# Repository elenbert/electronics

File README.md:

Repository for my electronics projects:

* allsky camera
* ztsh autoguide system
* power supply

CAD: Eagle Version 7.2.0 for Linux

Additional: schematic png's

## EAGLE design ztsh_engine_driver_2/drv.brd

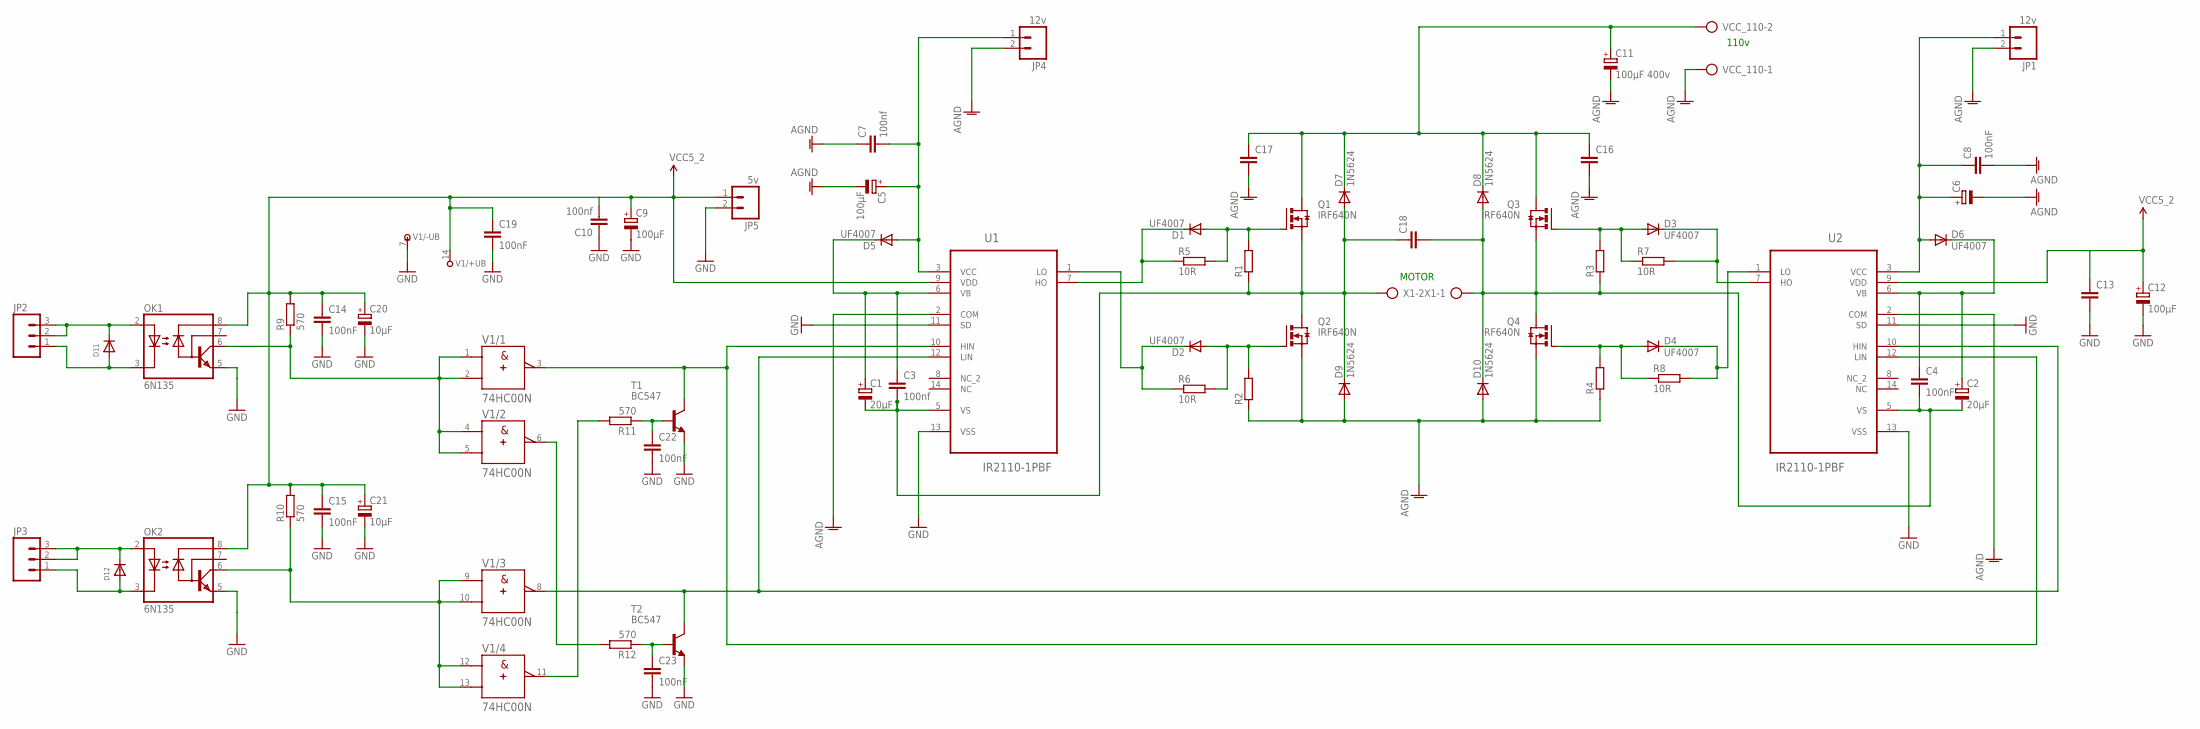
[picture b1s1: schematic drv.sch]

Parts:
C1, C2: 20µF; E2,5-6E
C3, C10: 100nf; C0805
C4: 100nF; C0504
C5, C9, C12: 100µF; E2-5
C6: CPOL-EUE2-5; E2-5
C7: 100nf; C1310
C8, C14, C15, C19, C22, C23: 100nF; C0805
C11: 100µF 400v; EB25D
C13: C-EUC0805; C0805
C16, C17: C5/3; C5B3
C18: C-EU150-091X182; C150-091X182
C20, C21: 10µF; E2-5
D1, D2, D3, D4, D5, D6: UF4007; DIODE-1N4001-KIT
D7, D8, D9, D10: 1N5624; DO201-15
D11, D12: DIODEDO-1N4148; DO-1N4148
JP1, JP4: 12v; JST-2-PTH-VERT
JP2, JP3: M03LOCK; 1X03_LOCK
JP5: 5v; JST-2-PTH-VERT
OK1, OK2: 6N135; DIL08
Q1, Q2, Q3, Q4: IRF640N; TO262-V
R1, R2, R3, R4: R-EU_0207/12; 0207/12
R5, R6, R7, R8: 10R; 0207/12
R9, R10, R11, R12: 570; R0805
T1, T2: BC547; TO92
U1, U2: IR2110-1PBF; DIP254P762X533-14
V1: 74HC00N; DIL14
VCC_110: AK300/2
X1: AK300/2

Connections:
AGND: C5.-, C6.-, C7.1, C8.2, C11.-, C16.2, C17.2, D9.A, D10.A, JP1.2, JP4.2, Q2.3 (S), Q4.3 (S), R2.1, R4.1, U1.2 (COM), U2.2 (COM), VCC_110.1
GND: C9.-, C10.1, C12.-, C13.2, C14.2, C15.2, C19.2, C20.-, C21.-, C22.2, C23.2, JP5.2, T1.1 (E), T2.1 (E), U1.11 (SD), U1.13 (VSS), U2.11 (SD), U2.13 (VSS), V1.7 (-UB)
unnamed: D1.A, Q1.1 (G), R1.2, R5.2
unnamed: D11.C, JP2.2, JP2.3, OK1.2 (A)
unnamed: D2.A, Q2.1 (G), R2.2, R6.2
unnamed: D1.C, R5.1, U1.7 (HO)
unnamed: D11.A, JP2.1, OK1.3 (C)
unnamed: D2.C, R6.1, U1.1 (LO)
unnamed: OK2.6 (VO), R10.1, V1.9 (A), V1.10 (B), V1.12 (A), V1.13 (B)
unnamed: D3.A, Q3.1 (G), R3.2, R7.1
unnamed: D3.C, R7.2, U2.7 (HO)
unnamed: D4.C, R8.2, U2.1 (LO)
unnamed: D12.A, JP3.1, OK2.3 (C)
unnamed: OK1.6 (VO), R9.1, V1.1 (A), V1.2 (B), V1.4 (A), V1.5 (B)
unnamed: D4.A, Q4.1 (G), R4.2, R8.1
unnamed: C1.+, C3.1, D5.C, U1.6 (VB)
unnamed: T1.3 (C), U1.10 (HIN), U2.12 (LIN), V1.3 (Y)
unnamed: C2.+, C4.1, D6.C, U2.6 (VB)
unnamed: T2.3 (C), U1.12 (LIN), U2.10 (HIN), V1.8 (Y)
unnamed: R11.2, V1.11 (Y)
unnamed: C22.1, R11.1, T1.2 (B)
unnamed: C23.1, R12.1, T2.2 (B)
unnamed: R12.2, V1.6 (Y)
unnamed: D12.C, JP3.2, JP3.3, OK2.2 (A)
OUT1: C2.-, C4.2, C18.2, D8.A, D10.C, Q3.3 (S), Q4.2 (D), R3.1, U2.5 (VS), X1.1
OUT2: C1.-, C3.2, C18.1, D7.A, D9.C, Q1.3 (S), Q2.2 (D), R1.1, U1.5 (VS), X1.2
VCC: C9.+, C10.2, C12.+, C13.1, C14.1, C15.1, C19.1, C20.+, C21.+, JP5.1, OK1.8 (VCC), OK2.8 (VCC), R9.2, R10.2, U1.9 (VDD), U2.9 (VDD), V1.14 (+UB)
VCC_12_1: C5.+, C7.2, D5.A, JP4.1, U1.3 (VCC)
VCC_12_2: C6.+, C8.1, D6.A, JP1.1, U2.3 (VCC)
VCC_110: C11.+, C16.1, C17.1, D7.C, D8.C, Q1.2 (D), Q3.2 (D), VCC_110.2

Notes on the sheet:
110v
MOTOR

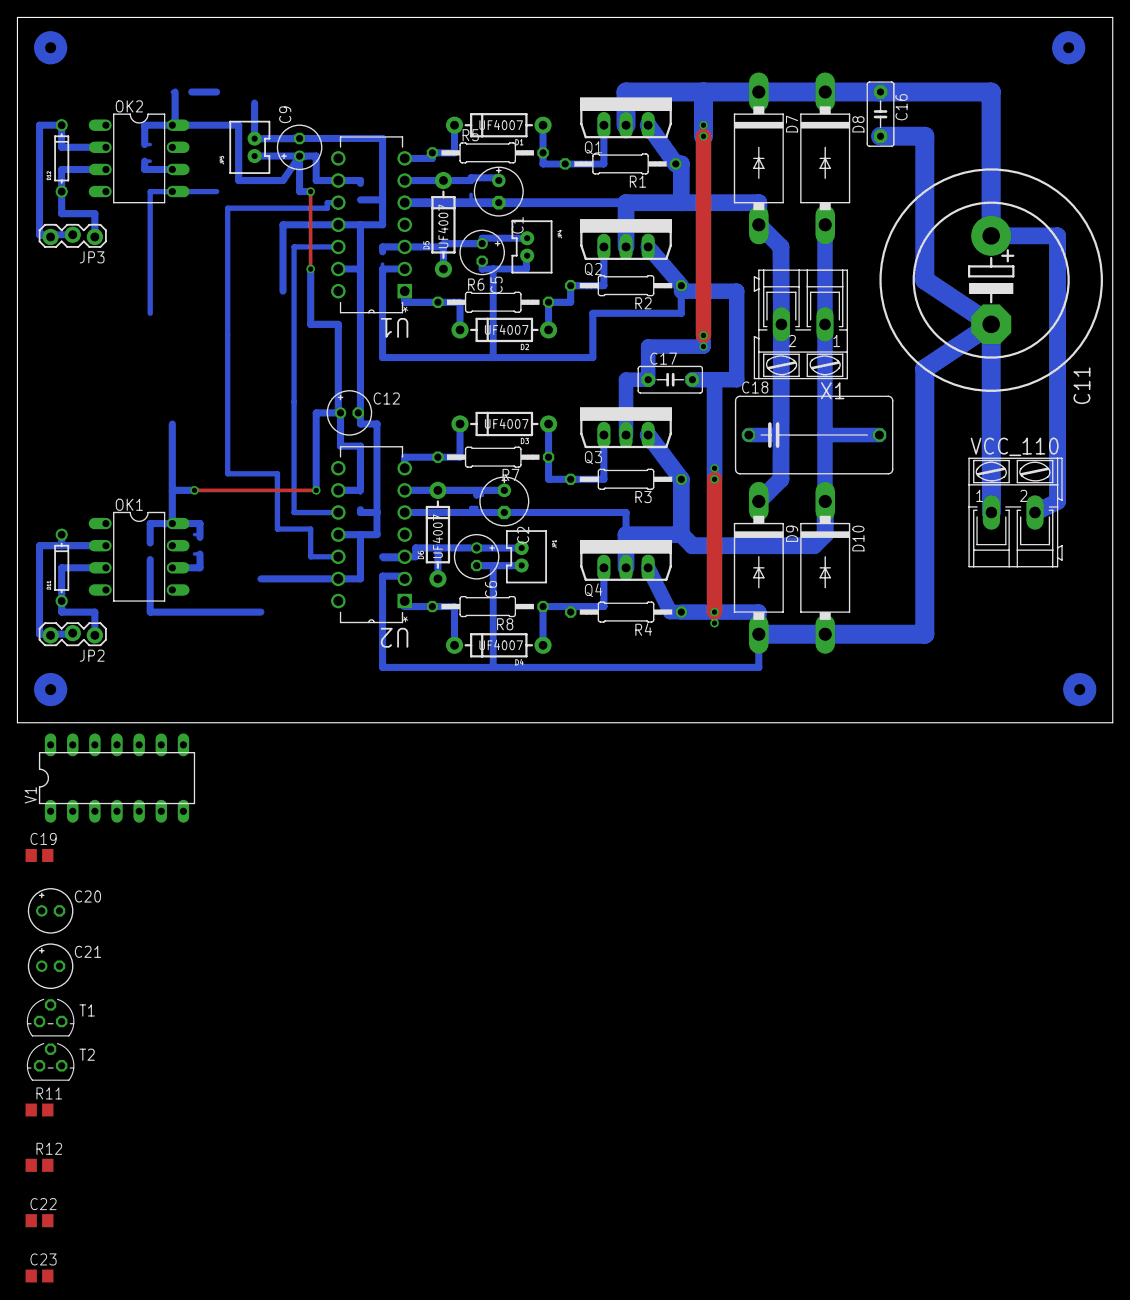
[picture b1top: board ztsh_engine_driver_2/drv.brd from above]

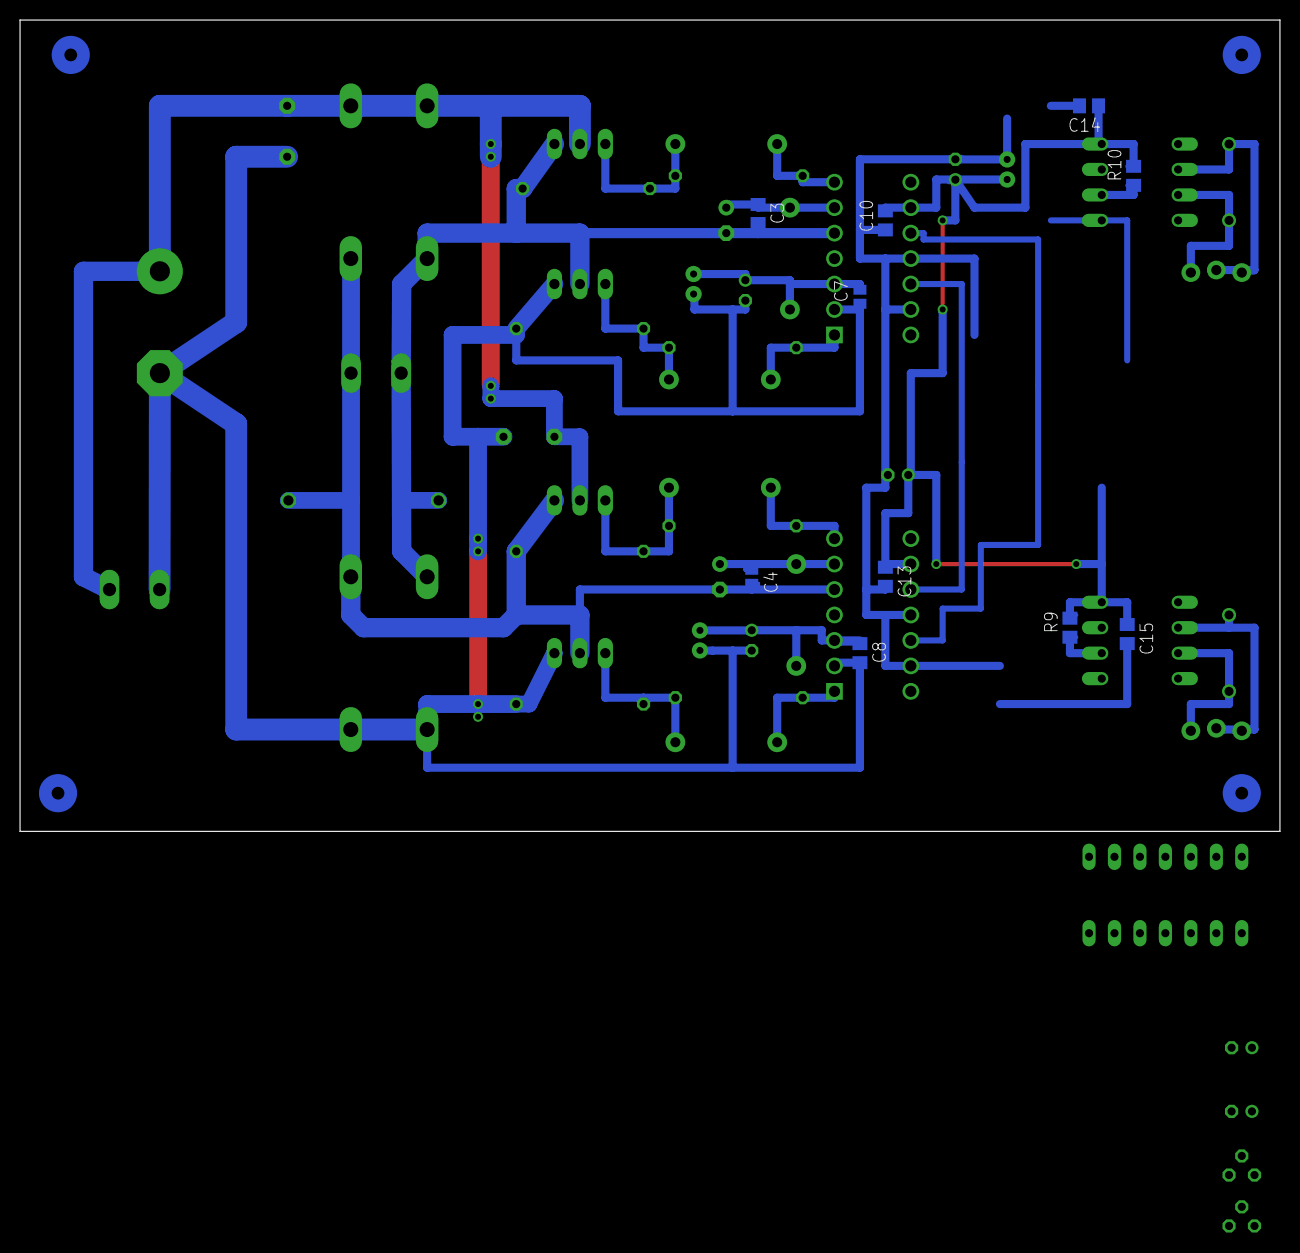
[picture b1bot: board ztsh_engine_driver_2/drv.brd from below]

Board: 2 copper layers, 125.7 x 80.9 mm, 65 parts (10 on the bottom side), 30 nets.

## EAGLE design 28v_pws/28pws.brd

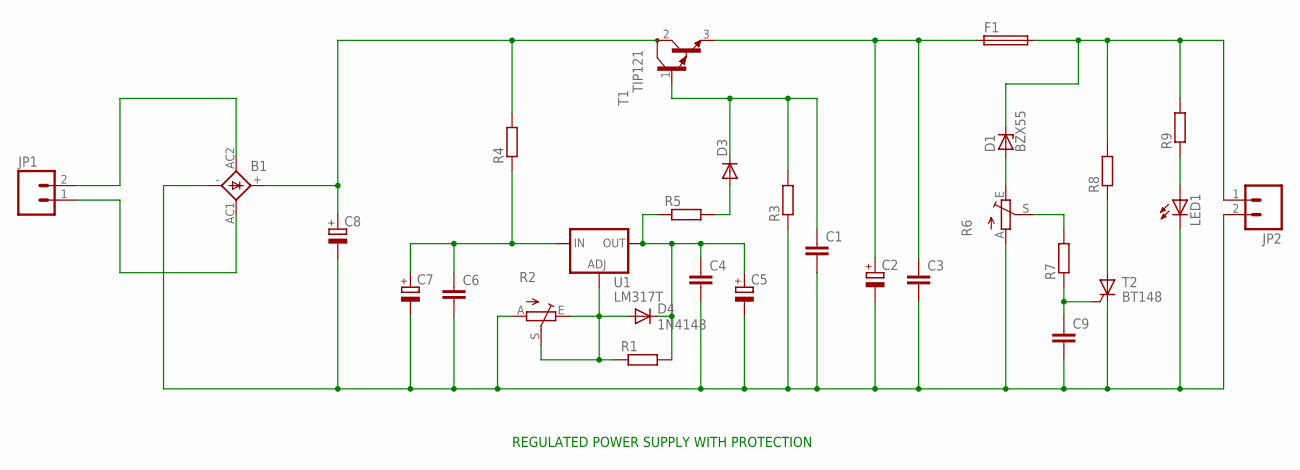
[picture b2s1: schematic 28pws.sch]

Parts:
B1: GBU4S
C1, C3, C4, C6, C9: C-EU025-025X050; C025-025X050
C2: CPOL-EUE5-13; E5-13
C5, C7: CPOL-EUE2.5-5; E2,5-5
C8: CPOL-EUE7.5-16; E7,5-16
D1: BZX55; DO35Z10
D3: DIODE-DO41-7.6; DO41-7.6
D4: 1N4148; DO35-7
F1: 19560
JP1, JP2: M02POGO_PIN_HOLES_ONLY; 1X02_PP_HOLES_ONLY
LED1: LED5MM
R1, R9: R-EU_0204/7; 0204/7
R2: TRIM_EU-RJ9W; RJ9W
R3, R5: R-EU_0204/2V; 0204V
R4: R-EU_0411/3V; 0411V
R6: TRIM_EU-B25P; B25P
R7: R-EU_0207/10; 0207/10
R8: R-EU_VTA54; VTA54
T1: TIP121; TO220
T2: BT148; SOT82S
U1: LM317T; TO220-ADJ

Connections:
GND: B1.-, C1.2, C2.-, C3.2, C4.2, C5.-, C6.2, C7.-, C8.-, C9.2, JP2.2, LED1.K (C), R2.A, R3.1, R6.A, T2.C
unnamed: C1.1, D3.C, R3.2, T1.1 (B)
unnamed: D1.C, F1.2, JP2.1, R8.2, R9.2
unnamed: R6.S, R7.2
unnamed: C2.+, C3.1, F1.1, T1.3 (E)
unnamed: C4.1, C5.+, D4.C, R1.2, R5.1, U1.OUT
unnamed: C6.1, C7.+, R4.1, U1.IN
unnamed: D4.A, R1.1, R2.E, R2.S, U1.ADJ
unnamed: B1.AC2 (AC1), JP1.2
unnamed: D3.A, R5.2
unnamed: B1.+, C8.+, R4.2, T1.2 (C)
unnamed: B1.AC1 (AC2), JP1.1
unnamed: C9.1, R7.1, T2.G
unnamed: D1.A, R6.E
unnamed: LED1.A, R9.1
unnamed: R8.1, T2.A

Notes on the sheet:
REGULATED POWER SUPPLY WITH PROTECTION

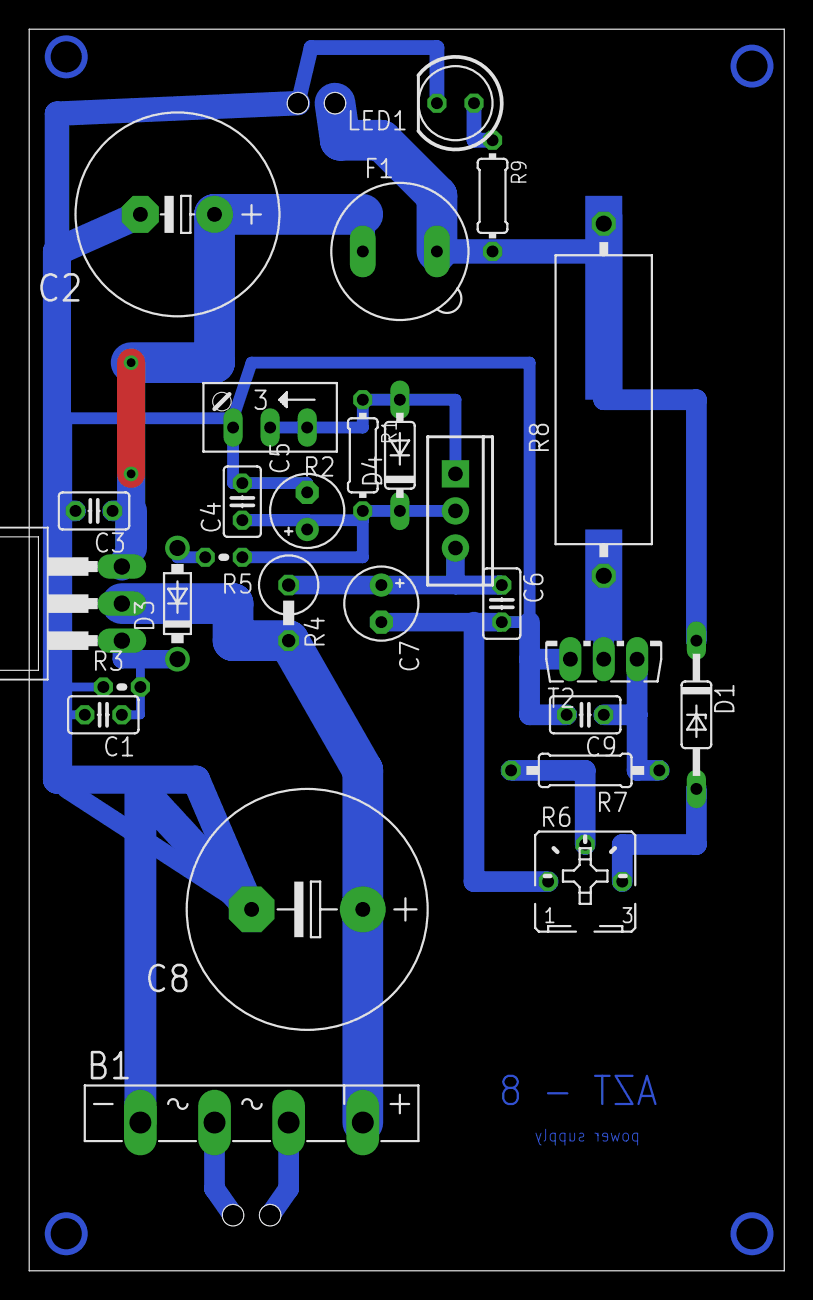
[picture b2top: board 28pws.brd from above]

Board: 2 copper layers, 51.7 x 85.1 mm, 29 parts (0 on the bottom side), 16 nets.

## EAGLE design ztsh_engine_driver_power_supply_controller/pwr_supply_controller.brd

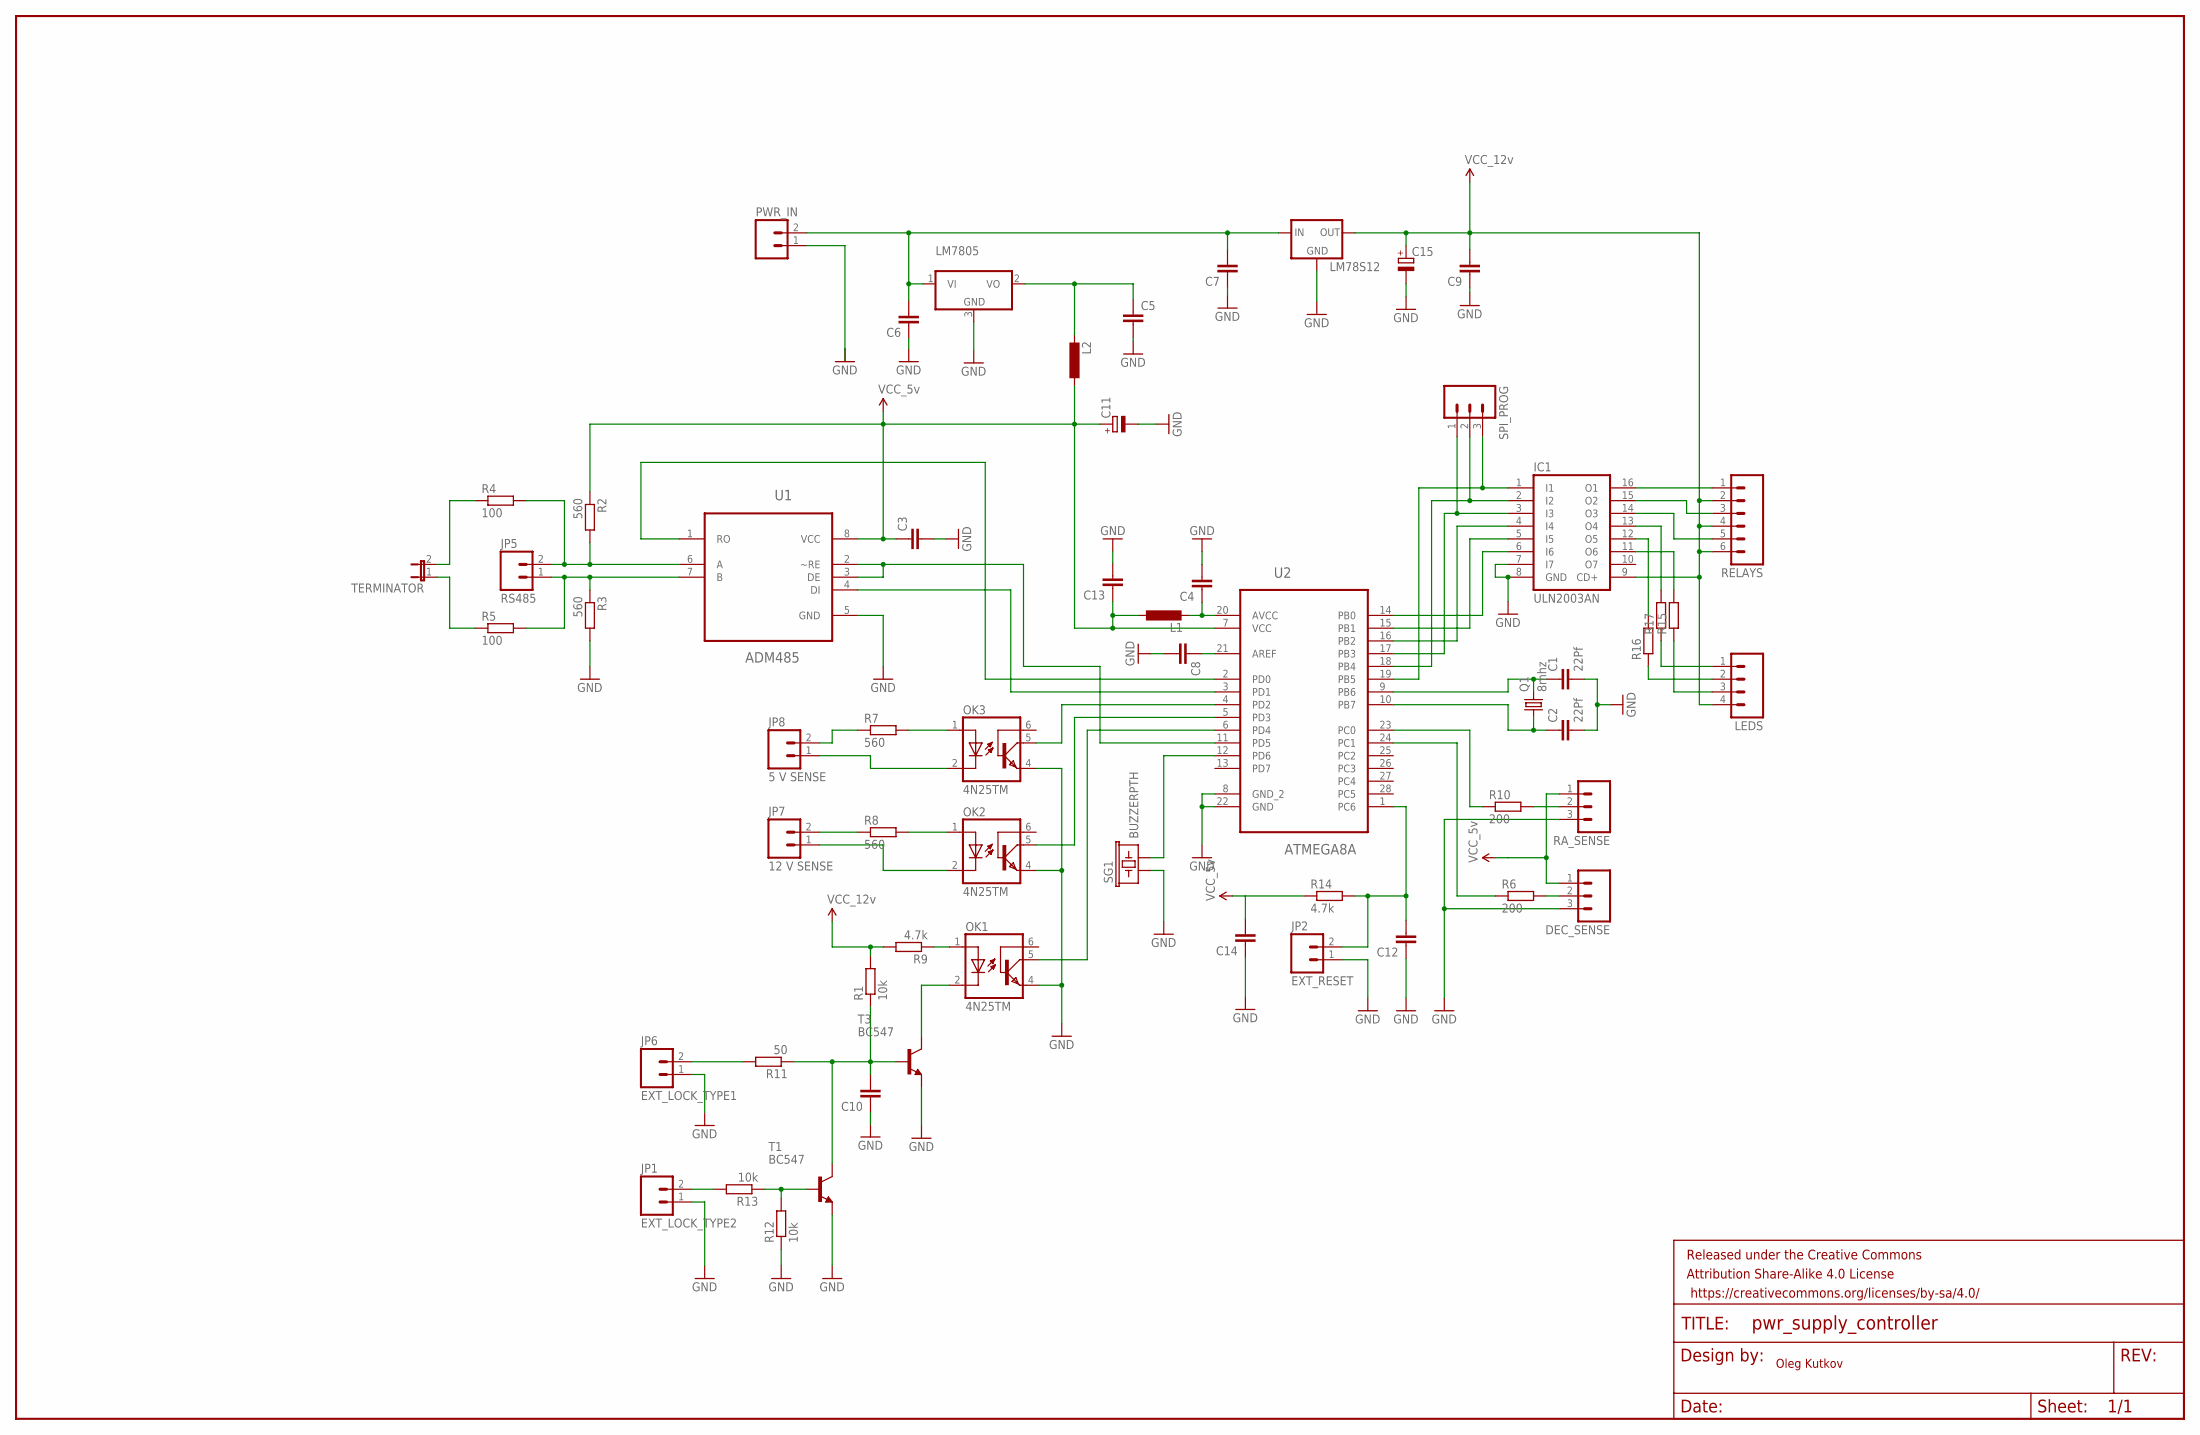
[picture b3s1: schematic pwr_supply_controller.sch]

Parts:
C1, C2: 22Pf; C0603K
C3, C4, C5, C8, C10, C12, C13, C14: C-EUC0603K; C0603K
C6, C7, C9: C-EUC0805; C0805
C11: CPOL-EUE2-5; E2-5
C15: CPOL-EUE3.5-8; E3,5-8
DEC_SENSE: M03PTH; 1X03
FRAME1: FRAME-LEDGER; CREATIVE_COMMONS
IC1: ULN2003AN; DIL16
JP1: EXT_LOCK_TYPE2; JST-2-PTH-VERT
JP2: EXT_RESET; 1X02
JP5: RS485; JST-2-PTH-VERT
JP6: EXT_LOCK_TYPE1; JST-2-PTH-VERT
JP7: 12 V SENSE; JST-2-PTH-VERT
JP8: 5 V SENSE; JST-2-PTH-VERT
L1, L2: L-EU0204/7; 0204/7
LEDS: M04PTH; 1X04
LM78S12: V_REG_78XX-TO-220; TO-220-ALT
LM7805: 7808DT; TO252
OK1, OK2, OK3: 4N25TM; DIL6-04
PWR_IN: M02JST-PTH-VERT; JST-2-PTH-VERT
Q1: 8mhz; HC49/S
R1, R12, R13: 10k; 0204/7
R2, R3: 560; M0805
R4: 100; R0805
R5: 100; M0805
R6, R10: 200; M0805
R7, R8: 560; 0204/7
R9: 4.7k; 0204/7
R11: 50; 0204/7
R14: 4.7k; M0805
R15, R16, R17: R-EU_M0805; M0805
RA_SENSE: M03PTH; 1X03
RELAYS: M06POLAR; MOLEX-1X6
SG1: BUZZERPTH; BUZZER-12MM
SPI_PROG: M03PTH; 1X03
T1, T3: BC547; TO92
TERMINATOR: JUMPER-2PTH_LOCK; 1X02_LOCK
U1: ADM485; SOIC127P600X175-8N
U2: ATMEGA8A; DIP254P762X457-28

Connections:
GND: C1.2, C2.2, C3.2, C4.2, C5.2, C6.1, C7.1, C8.2, C9.1, C10.1, C11.-, C12.1, C13.2, C14.1, C15.-, DEC_SENSE.3, IC1.7 (I7), IC1.8 (GND), JP1.1, JP2.1, JP6.1, LM78S12.GND, LM7805.3 (GND), OK1.4 (EMI), OK2.4 (EMI), OK3.4 (EMI), PWR_IN.1, R3.2, R12.1, RA_SENSE.3, SG1.+ (1), T1.1 (E), T3.1 (E), U1.5 (GND), U2.8 (GND_2), U2.22 (GND)
unnamed: C1.1, Q1.2, U2.9 (PB6)
unnamed: C2.1, Q1.1, U2.10 (PB7)
unnamed: OK3.5 (COL), U2.4 (PD2)
unnamed: OK2.5 (COL), U2.5 (PD3)
unnamed: OK3.1 (A), R7.2
unnamed: OK1.5 (COL), U2.6 (PD4)
unnamed: C4.1, L1.2, U2.20 (AVCC)
unnamed: R10.2, RA_SENSE.2
unnamed: U1.1 (RO), U2.2 (PD0)
unnamed: C8.1, U2.21 (AREF)
unnamed: U1.4 (DI), U2.3 (PD1)
unnamed: U1.2 (~RE), U1.3 (DE), U2.11 (PD5)
unnamed: JP5.2, R2.2, R4.2, U1.6 (A)
unnamed: JP5.1, R3.1, R5.2, U1.7 (B)
unnamed: R4.1, TERMINATOR.2
unnamed: R5.1, TERMINATOR.1
unnamed: C6.2, C7.2, LM78S12.IN, LM7805.1 (VI), PWR_IN.2
unnamed: DEC_SENSE.2, R6.2
unnamed: IC1.6 (I6), U2.14 (PB0)
unnamed: IC1.5 (I5), U2.15 (PB1)
unnamed: IC1.4 (I4), U2.16 (PB2)
unnamed: IC1.3 (I3), SPI_PROG.1, U2.17 (PB3)
unnamed: IC1.2 (I2), SPI_PROG.2, U2.18 (PB4)
unnamed: IC1.1 (I1), SPI_PROG.3, U2.19 (PB5)
unnamed: R10.1, U2.23 (PC0)
unnamed: R6.1, U2.24 (PC1)
unnamed: IC1.16 (O1), RELAYS.1
unnamed: IC1.15 (O2), RELAYS.3
unnamed: IC1.14 (O3), RELAYS.5
unnamed: JP6.2, R11.2
unnamed: LEDS.1, R17.1
unnamed: LEDS.2, R16.1
unnamed: IC1.11 (O6), R15.2
unnamed: SG1.- (2), U2.12 (PD6)
unnamed: JP8.2, R7.1
unnamed: JP8.1, OK3.2 (C)
unnamed: OK2.1 (A), R8.2
unnamed: JP7.2, R8.1
unnamed: JP7.1, OK2.2 (C)
unnamed: C10.2, R1.1, R11.1, T1.3 (C), T3.2 (B)
unnamed: R12.2, R13.1, T1.2 (B)
unnamed: OK1.1 (A), R9.1
unnamed: C5.1, L2.2, LM7805.2 (VO)
unnamed: OK1.2 (C), T3.3 (C)
unnamed: JP1.2, R13.2
unnamed: C12.2, JP2.2, R14.2, U2.1 (PC6)
unnamed: IC1.12 (O5), R16.2
unnamed: IC1.13 (O4), R17.2
unnamed: LEDS.3, R15.1
VCC: C3.1, C11.+, C13.1, C14.2, DEC_SENSE.1, L1.1, L2.1, R2.1, R14.1, RA_SENSE.1, U1.8 (VCC), U2.7 (VCC)
VDD: C9.2, C15.+, IC1.9 (CD+), LEDS.4, LM78S12.OUT, R1.2, R9.2, RELAYS.2, RELAYS.4, RELAYS.6

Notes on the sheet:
Oleg Kutkov

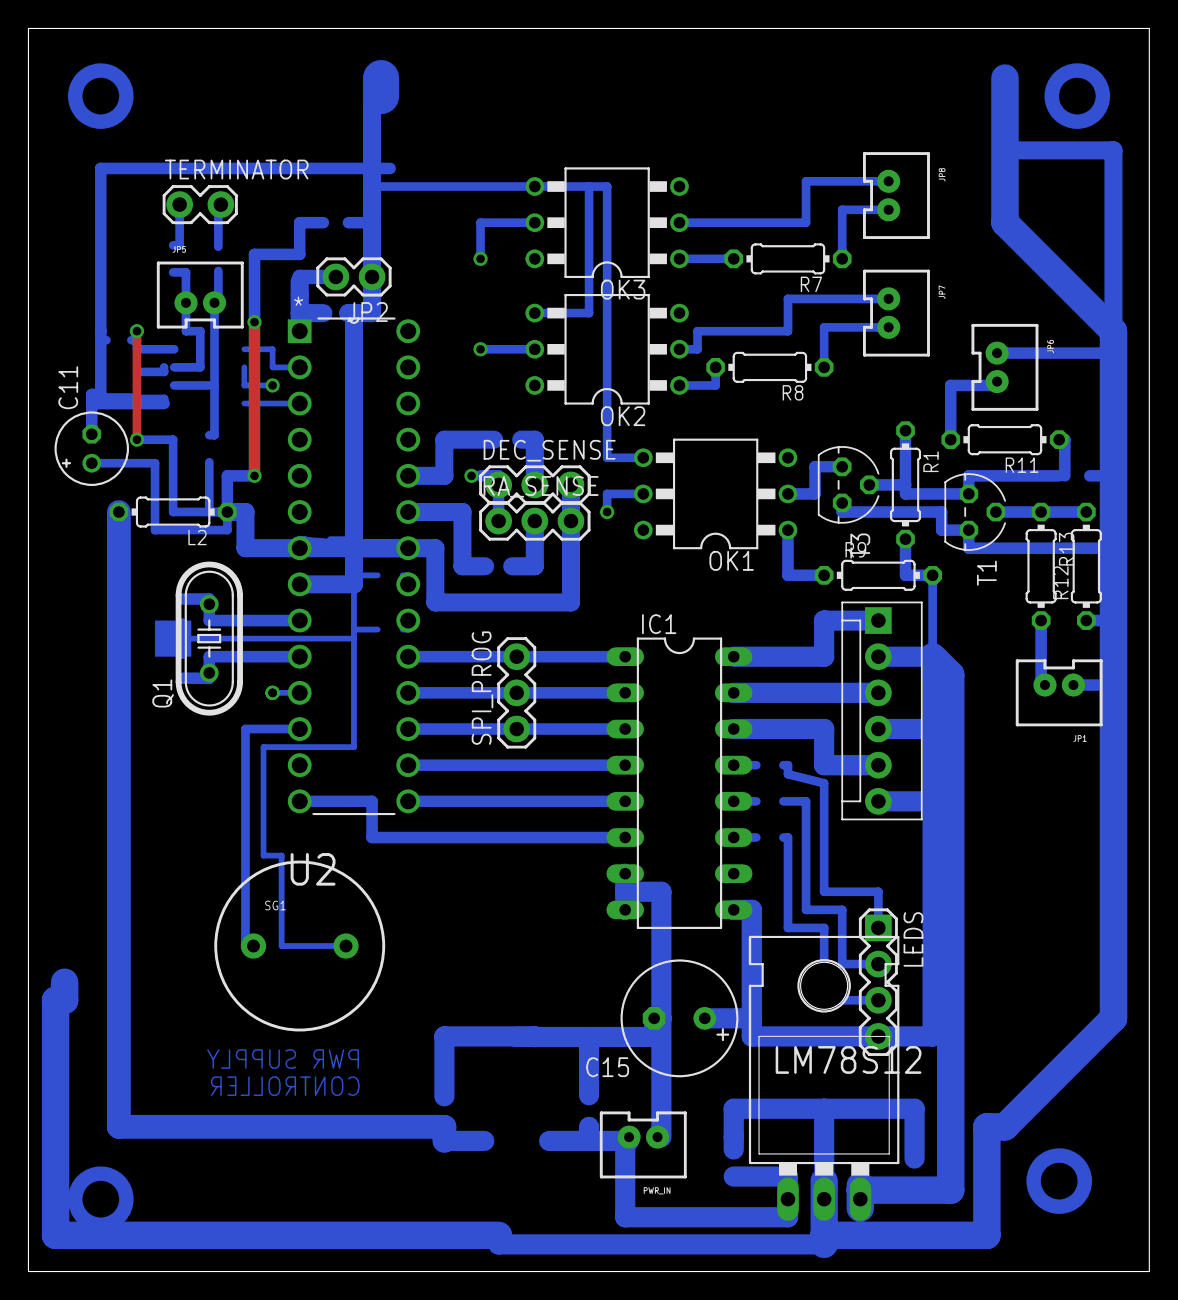
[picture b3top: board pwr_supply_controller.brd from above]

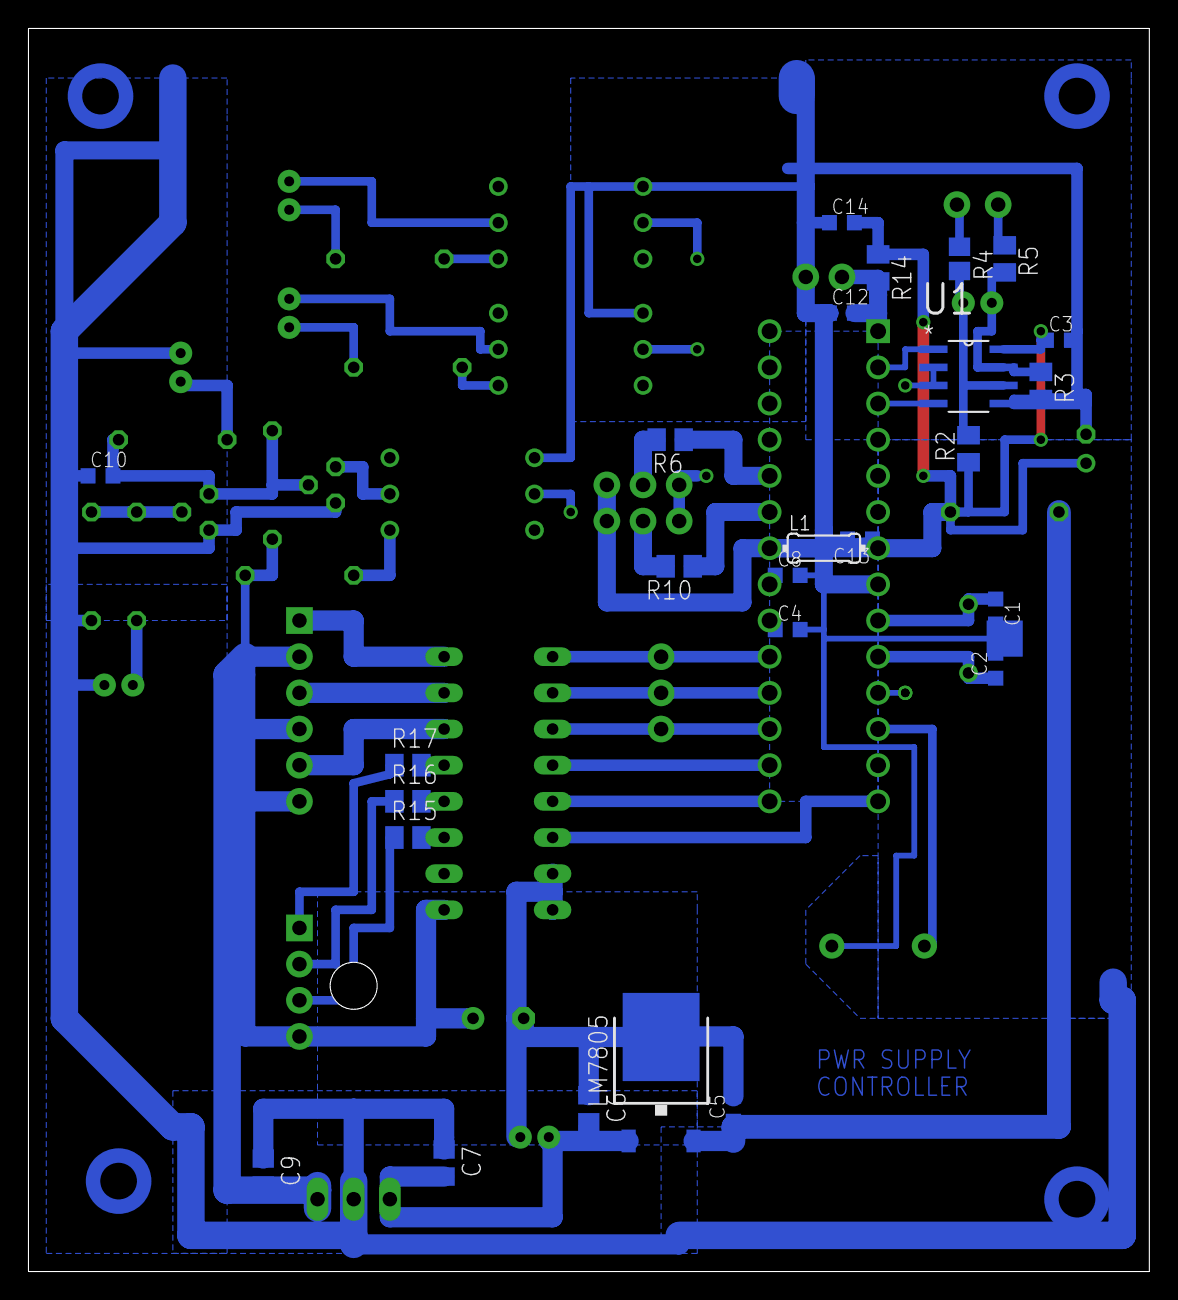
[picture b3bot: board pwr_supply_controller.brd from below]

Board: 2 copper layers, 78.7 x 87.3 mm, 60 parts (26 on the bottom side), 52 nets.

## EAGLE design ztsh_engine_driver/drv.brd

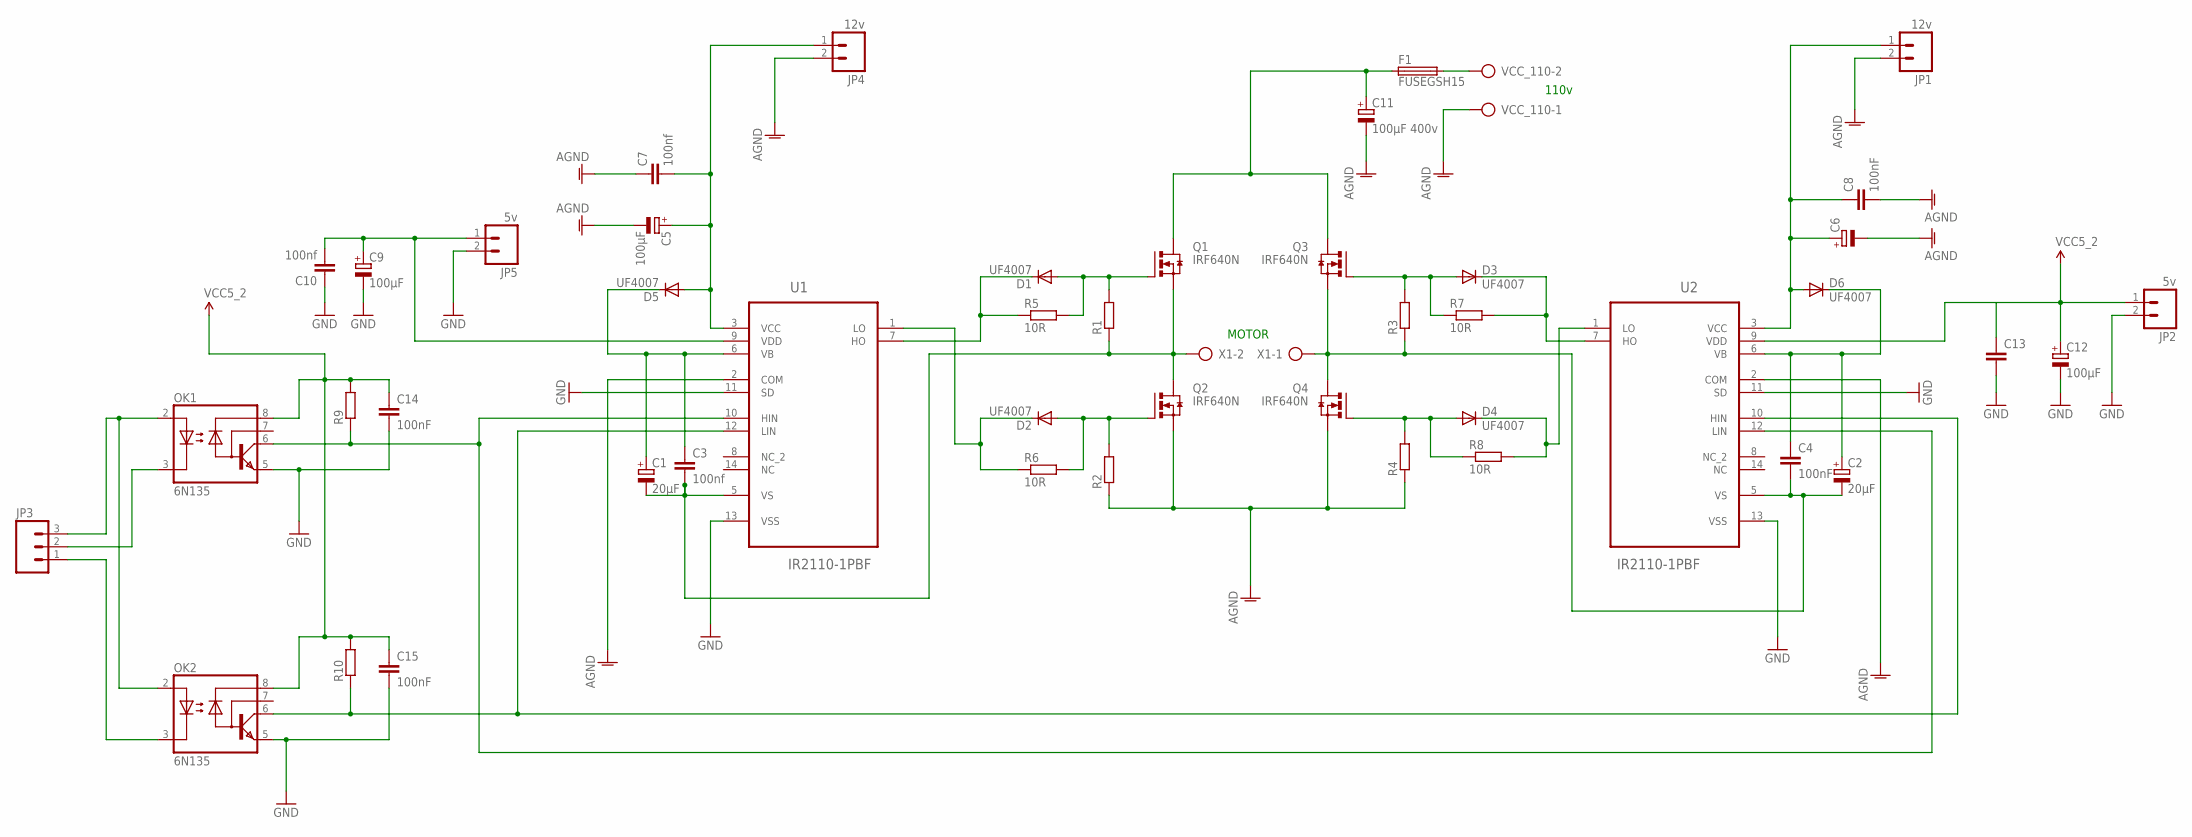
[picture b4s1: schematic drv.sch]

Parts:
C1, C2: 20µF; E2,5-6E
C3, C10: 100nf; C0805
C4: 100nF; C0504
C5, C9, C12: 100µF; E2-5
C6: CPOL-EUE2-5; E2-5
C7: 100nf; C1310
C8, C14, C15: 100nF; C0805
C11: 100µF 400v; EB25D
C13: C-EUC0805; C0805
D1, D2, D3, D4, D5, D6: UF4007; DIODE-1N4001-KIT
F1: FUSEGSH15; GSH15
JP1, JP4: 12v; JST-2-PTH-VERT
JP2, JP5: 5v; JST-2-PTH-VERT
JP3: M03LOCK; 1X03_LOCK
OK1, OK2: 6N135; DIL08
Q1, Q2, Q3, Q4: IRF640N; TO220AH
R1, R2, R3, R4: R-EU_0207/12; 0207/12
R5, R6, R7, R8: 10R; 0207/12
R9, R10: R-EU_R0805; R0805
U1, U2: IR2110-1PBF; DIP254P762X533-14
VCC_110: AK300/2
X1: AK300/2

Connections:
110_1: F1.2, VCC_110.2
AGND: C5.-, C6.-, C7.1, C8.2, C11.-, JP1.2, JP4.2, Q2.E (S), Q4.E (S), R2.1, R4.1, U1.2 (COM), U2.2 (COM), VCC_110.1
GND: C9.-, C10.1, C12.-, C13.2, C14.2, C15.2, JP2.2, JP5.2, OK1.5 (GND), OK2.5 (GND), U1.11 (SD), U1.13 (VSS), U2.11 (SD), U2.13 (VSS)
unnamed: D1.A, Q1.B (G), R1.2, R5.2
unnamed: JP3.3, OK1.2 (A), OK2.2 (A)
unnamed: D2.A, Q2.B (G), R2.2, R6.2
unnamed: D1.C, R5.1, U1.7 (HO)
unnamed: JP3.2, OK1.3 (C)
unnamed: D2.C, R6.1, U1.1 (LO)
unnamed: D3.A, Q3.B (G), R3.2, R7.1
unnamed: D3.C, R7.2, U2.7 (HO)
unnamed: D4.C, R8.2, U2.1 (LO)
unnamed: JP3.1, OK2.3 (C)
unnamed: D4.A, Q4.B (G), R4.2, R8.1
unnamed: C1.+, C3.1, D5.C, U1.6 (VB)
unnamed: C2.+, C4.1, D6.C, U2.6 (VB)
unnamed: OK1.6 (VO), R9.1, U1.10 (HIN), U2.12 (LIN)
unnamed: OK2.6 (VO), R10.1, U1.12 (LIN), U2.10 (HIN)
OUT1: C2.-, C4.2, Q3.E (S), Q4.C (D), R3.1, U2.5 (VS), X1.1
OUT2: C1.-, C3.2, Q1.E (S), Q2.C (D), R1.1, U1.5 (VS), X1.2
VCC5_2: C12.+, C13.1, C14.1, C15.1, JP2.1, OK1.8 (VCC), OK2.8 (VCC), R9.2, R10.2, U2.9 (VDD)
VCC_5_1: C9.+, C10.2, JP5.1, U1.9 (VDD)
VCC_12_1: C5.+, C7.2, D5.A, JP4.1, U1.3 (VCC)
VCC_12_2: C6.+, C8.1, D6.A, JP1.1, U2.3 (VCC)
VCC_110: C11.+, F1.1, Q1.C (D), Q3.C (D)

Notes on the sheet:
110v
MOTOR

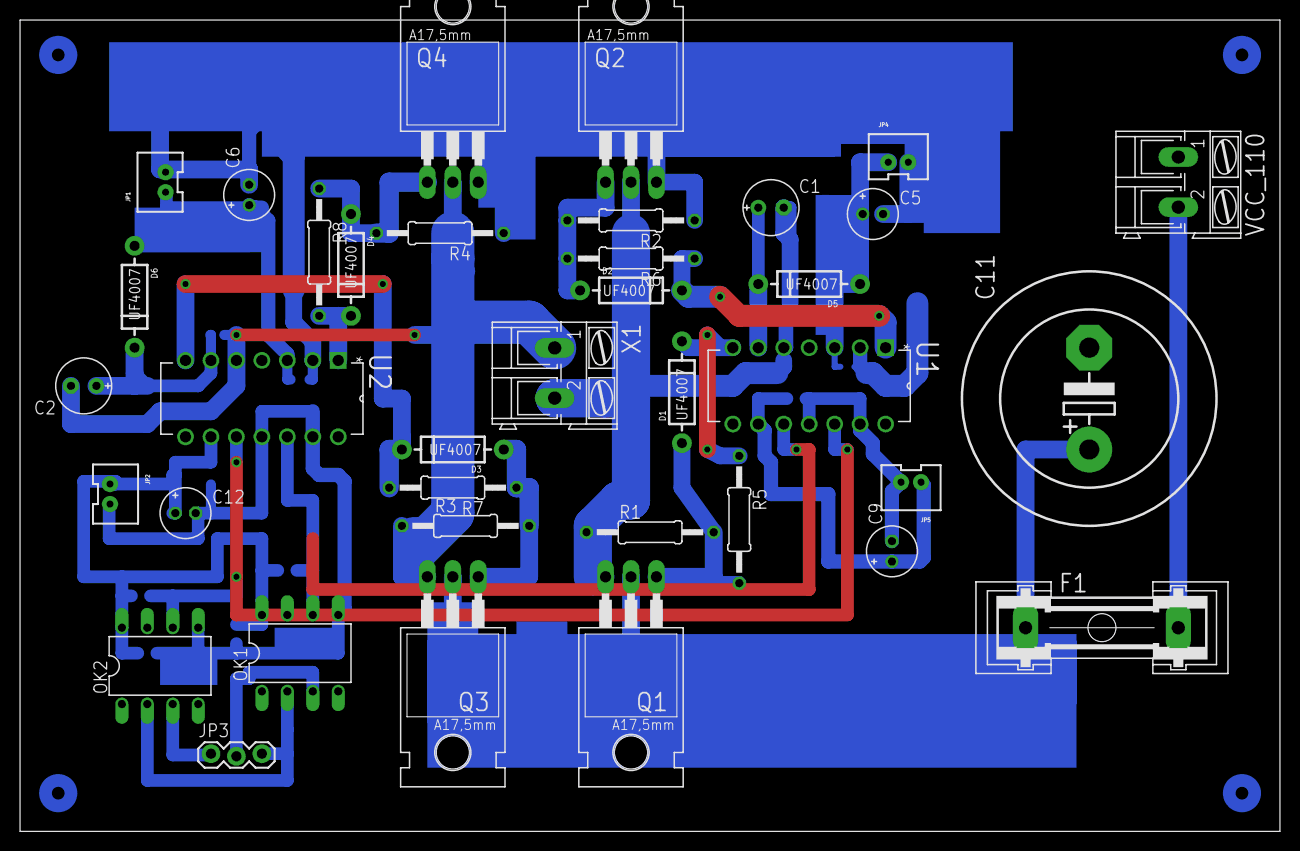
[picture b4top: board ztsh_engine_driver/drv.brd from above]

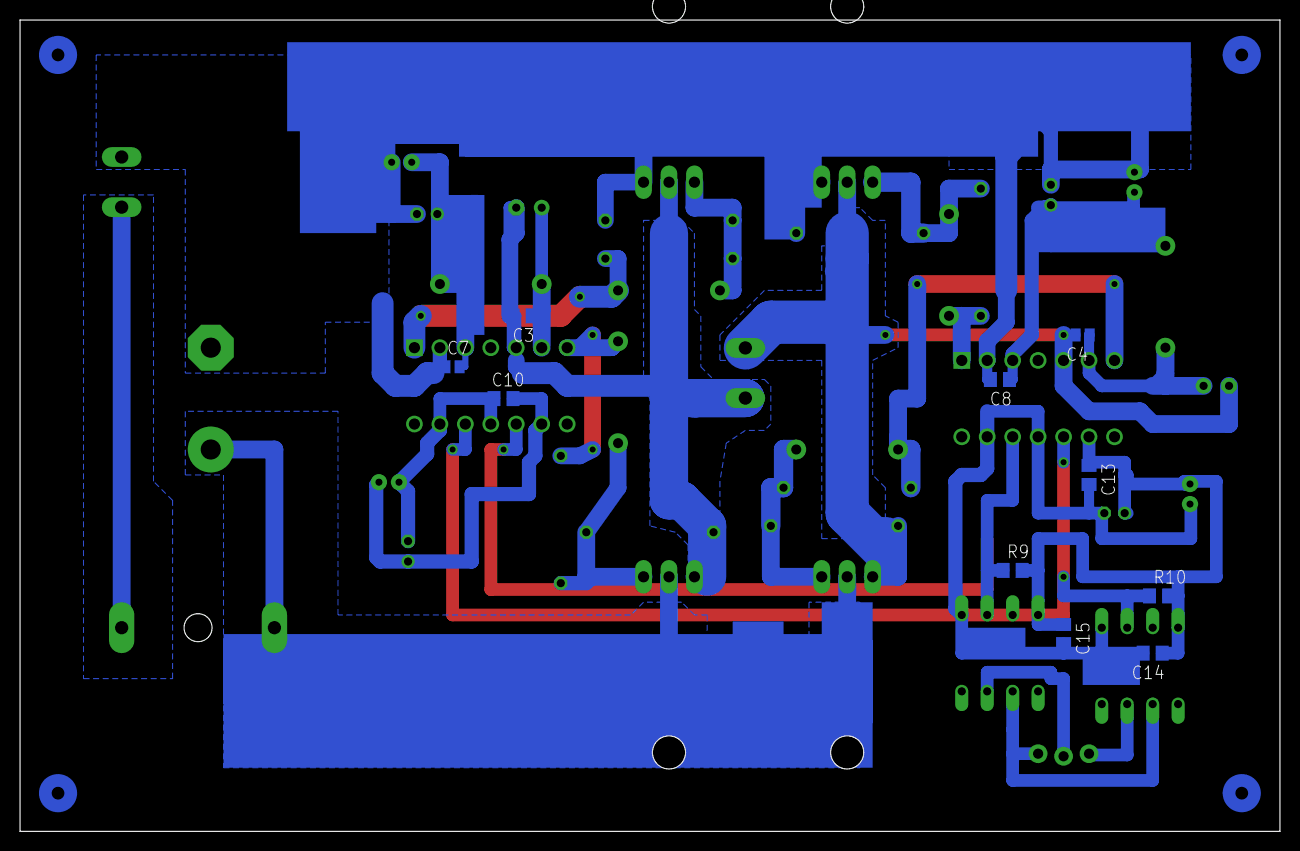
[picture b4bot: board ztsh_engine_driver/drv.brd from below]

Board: 2 copper layers, 125.7 x 80.9 mm, 47 parts (10 on the bottom side), 25 nets.

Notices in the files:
parts and their libraries:
SparkFun-Connectors: Licensing: Creative Commons ShareAlike 4.0 International - https://creativecommons.org/licenses/by-sa/4.0
SparkFun-Aesthetics: Released under the Creative Commons Attribution Share-Alike 4.0 License
SparkFun-Aesthetics: https://creativecommons.org/licenses/by-sa/4.0
